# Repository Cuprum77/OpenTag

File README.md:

# OpenTag

OpenTag is a project for building custom Bluetooth location finding beacons based on existing Apple and Google location finding networks. This repository contains the hardware and firmware for and STM32WB5x/35xx based "Polyglot" tag that can use both Google and Apple finding networks simultaneously. The repository also contains 3D printable enclosures for the tag as well as a docker based web interface for aggregating the results from the different location fetching backends.

## Backends
We did not invent or even do anything novel in terms of reverse engineering the Apple and Google finding networks. Thus, we rely on third party implementations of both to do the heavy lifting needed to make this project feasible, in particular:
- [Macless-Haystack](https://github.com/dchristl/macless-haystack) Used for fetching location data from the Apple finding network.
- [GoogleFindMyTools](https://github.com/leonboe1/GoogleFindMyTools) Used as a base for the Google finding network backend. (Note: A fork with additional features such as key rotation, compound tags and more was created based on GoogleFindMyTools and is used in this project, the fork is available [here](https://github.com/diminDDL/OpenTagBridge)).

## Hardware
The hardware design (located in the [hardware](./hardware) directory) for the Polyglot tag is based on the STM32WB5x/35xx series of microcontrollers and is powered with a single CR2032 battery. When actively advertising payloads it consumes around 3mA, in deep sleep that number drops to 3uA. By default the tag wakes up every 10 seconds for a ~25ms long advertising window and with a single 230mAh CR2032 cell the tag is expected to last for about 2 years and 6 months. The parameters can be adjusted for different use cases and battery life tradeoffs. The following formula can be used to estimate battery lifetime:

$$
I_{\mathrm{avg}}=
I_{\mathrm{active}}\cdot\frac{t_{\mathrm{active}}}{T_{\mathrm{cycle}}}
+
I_{\mathrm{sleep}}\cdot\left(1-\frac{t_{\mathrm{active}}}{T_{\mathrm{cycle}}}\right)
$$

$$
\text{Battery Life (years)} =
\frac{C_{\mathrm{bat}}}{I_{\mathrm{avg}}\cdot 24 \cdot 365}
$$

or equivalently

$$
\text{Battery Life (years)} =
\frac{C_{\mathrm{bat}}}
{\left(
I_{\mathrm{active}}\cdot\frac{t_{\mathrm{active}}}{T_{\mathrm{cycle}}}
+
I_{\mathrm{sleep}}\cdot\left(1-\frac{t_{\mathrm{active}}}{T_{\mathrm{cycle}}}\right)
\right)\cdot 24 \cdot 365}
$$

Where by default the parameters are:

$$
I_{\mathrm{active}} = 3.0\ \text{mA}
$$

$$
I_{\mathrm{sleep}} = 0.003\ \text{mA}
$$

$$
t_{\mathrm{active}} = 24\ \text{ms}
$$

$$
T_{\mathrm{cycle}} = 10\ \text{s}
$$

$$
C_{\mathrm{bat}} = 230\ \text{mAh}
$$

There is also a large capacitor bank on the board, it is optional, however it contains enough energy for a few advertisement bursts which can prevent the tag from resetting in high vibration environments.

The tag uses an integrated single part matching network from ST and a PCB antenna offering quite consistent RF performance without the need for manual tuning. A 4 layer stackup is used for better RF performance, but it could be simplified to 2 layers and a thinner stackup if needed.

The board also includes 2 LEDs, 2 jumpers for debugging and programming and an SWD pad compatible with a Tag-Connect.

## Firmware
See the [software](./software) directory for the firmware source code, build and programming instructions.

## Mechanical
The [3d_models](./3d_models) directory contains the 3D models for the tag itself, and the [enclosures](./enclosures) directory contains 3D models for enclosures.

## Aggregation and Web Interface
*TODO*

# Disclaimer
> [!CAUTION]
> This project is provided for educational and research purposes only. The authors and contributors disclaim liability and do not condone illegal, unauthorized, or unethical use, including unauthorized tracking or invasions of privacy.
> 
> Use of this project is entirely at your own risk. Interacting with Google or Apple location networks in undocumented or unsupported ways may violate platform rules or terms of service and may result in account penalties, service restrictions, or other consequences. The authors and contributors disclaim liability for misuse of this repository and for any damages or consequences resulting from its use.

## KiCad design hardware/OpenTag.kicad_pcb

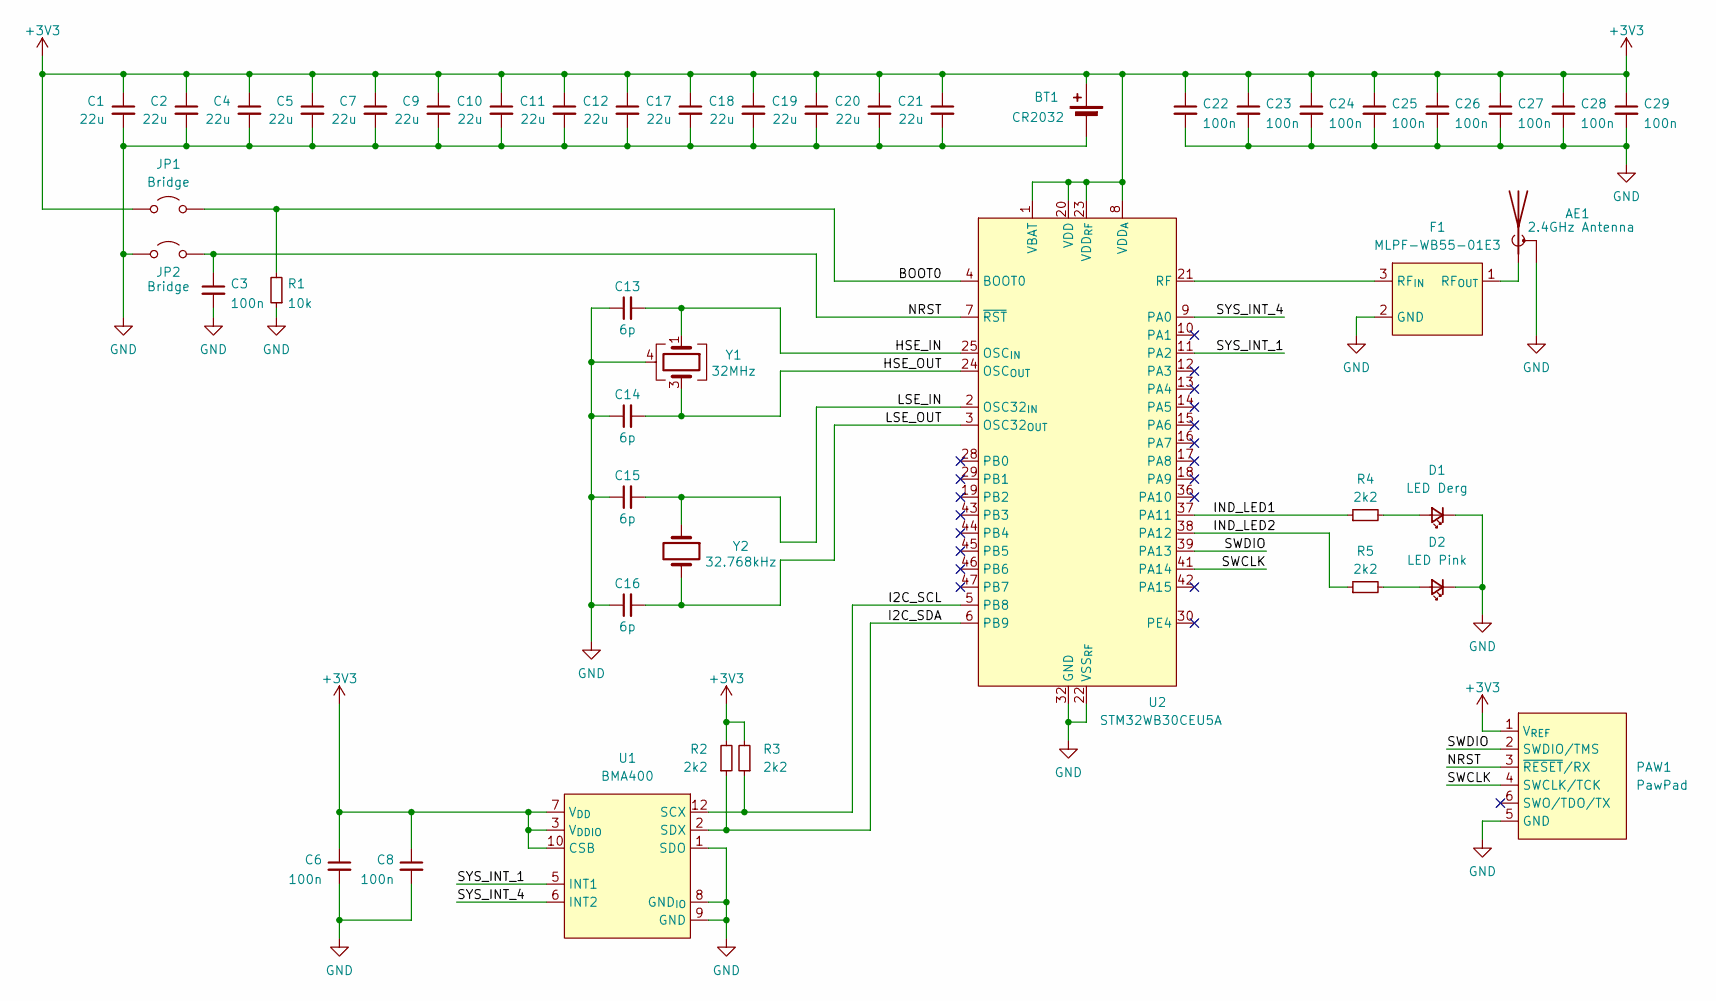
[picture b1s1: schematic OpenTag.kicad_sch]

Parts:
AE1: 2.4GHz Antenna; Texas_SWRA117D_2.4GHz_Right
BT1: CR2032; BAT-HLD-001
C1, C2, C4, C5, C7, C9, C10, C11, C12, C17, C18, C19, C20, C21: 22u; C_0805_2012Metric
C3, C6, C8, C22, C23, C24, C25, C26, C27, C28, C29: 100n; C_0402_1005Metric
C13, C14, C15, C16: 6p; C_0402_1005Metric
D1: LED Derg; LED_0805_2012Metric
D2: LED Pink; LED_0805_2012Metric
F1: MLPF-WB55-01E3; ST-Bumpless-CSP-6
JP1, JP2: Bridge; SolderJumper-2_P1.3mm_Open_RoundedPad1.0x1.5mm
PAW1: PawPad; Paw-Connect_RevB_TC2030-IDC-NL_2x03_P1.27mm_Vertical
R1: 10k; R_0402_1005Metric
R2, R3, R4, R5: 2k2; R_0402_1005Metric
U1: BMA400; LGA-12
U2: STM32WB30CEU5A; QFN-48-1EP_7x7mm_P0.5mm_EP5.45x5.45mm
Y1: 32MHz; Crystal_SMD_2016-4Pin_2.0x1.6mm
Y2: 32.768kHz; Crystal_SMD_3215-2Pin_3.2x1.5mm

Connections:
+3V3: BT1.1 (+), C1.1, C2.1, C4.1, C5.1, C6.1, C7.1, C8.1, C9.1, C10.1, C11.1, C12.1, C17.1, C18.1, C19.1, C20.1, C21.1, C22.1, C23.1, C24.1, C25.1, C26.1, C27.1, C28.1, C29.1, JP1.1 (A), PAW1.1 (V_{REF}), R2.2, R3.2, U1.3 (V_{DDIO}), U1.7 (V_{DD}), U1.10 (CSB), U2.1 (VBAT), U2.8 (VDD_{A}), U2.20 (VDD), U2.23 (VDD_{RF}), U2.31 (VDD), U2.33 (VDD), U2.34 (VDD), U2.35 (VDD), U2.40 (VDD), U2.48 (VDD)
/BOOT0: JP1.2 (B), R1.2, U2.4 (BOOT0)
/HSE_IN: C13.2, U2.25 (OSC_{IN}), Y1.1
/HSE_OUT: C14.2, U2.24 (OSC_{OUT}), Y1.3
/I2C_SCL: R3.1, U1.12 (SCX), U2.5 (PB8)
/I2C_SDA: R2.1, U1.2 (SDX), U2.6 (PB9)
/IND_LED1: R4.1, U2.37 (PA11)
/IND_LED2: R5.1, U2.38 (PA12)
/LSE_IN: C15.2, U2.2 (OSC32_{IN}), Y2.1
/LSE_OUT: C16.2, U2.3 (OSC32_{OUT}), Y2.2
/NRST: C3.1, JP2.2 (B), PAW1.3 (~RESET/RX), U2.7 (~RST)
/SWCLK: PAW1.4 (SWCLK/TCK), U2.41 (PA14)
/SWDIO: PAW1.2 (SWDIO/TMS), U2.39 (PA13)
/SYS_INT_1: U1.5 (INT1), U2.11 (PA2)
/SYS_INT_4: U1.6 (INT2), U2.9 (PA0)
GND: AE1.2 (Shield), BT1.2 (-), C1.2, C2.2, C3.2, C4.2, C5.2, C6.2, C7.2, C8.2, C9.2, C10.2, C11.2, C12.2, C13.1, C14.1, C15.1, C16.1, C17.2, C18.2, C19.2, C20.2, C21.2, C22.2, C23.2, C24.2, C25.2, C26.2, C27.2, C28.2, C29.2, D1.1 (K), D2.1 (K), F1.2 (GND), F1.4 (GND), F1.5 (GND), F1.6 (GND), JP2.1 (A), PAW1.5 (GND), R1.1, U1.1 (SDO), U1.8 (GND_{IO}), U1.9 (GND), U2.22 (VSS_{RF}), U2.32 (GND), U2.49 (EP), Y1.2, Y1.4
unnamed: AE1.1 (A), F1.1 (RF_{OUT})
unnamed: D1.2 (A), R4.2
unnamed: D2.2 (A), R5.2
unnamed: F1.3 (RF_{IN}), U2.21 (RF)

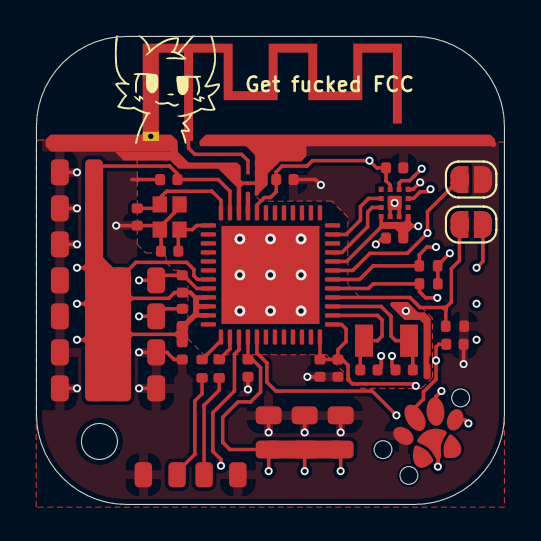
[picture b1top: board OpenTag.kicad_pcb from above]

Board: 4 copper layers, 26.0 x 26.0 mm, 46 parts (1 on the bottom side), 20 nets.

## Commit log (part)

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2024-11-26 added STM32CUBE project
2025-01-03 removed linker nonsense
2025-09-10 better readme and firmware with faster pings
2025-09-10 added images to be added to readme
2026-04-10 updated tag to support both apple and google updated docs
2026-04-10 Updated readme for GitHub styling
2026-04-10 fixed broken markdown
2026-04-13 added minimum viable combined dashboard webui
2026-04-29 updated webui
2026-05-01 updated webui interface, white/dark mode toggle and general polish
2026-05-01 updated webui to include history window section and other improvements
2026-05-01 updated webui and added better error handling and presentation
2026-05-04 improved error handling and alert displays in the webui
2026-06-27 Updated the Keys view
2026-06-27 updated UI and key handling slightly
2026-06-28 Added a tab for creating a "device" out of individual "tags"
